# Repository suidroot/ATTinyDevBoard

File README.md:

# ATTinyDevBoardv1
An ATTiny85 Dev Board

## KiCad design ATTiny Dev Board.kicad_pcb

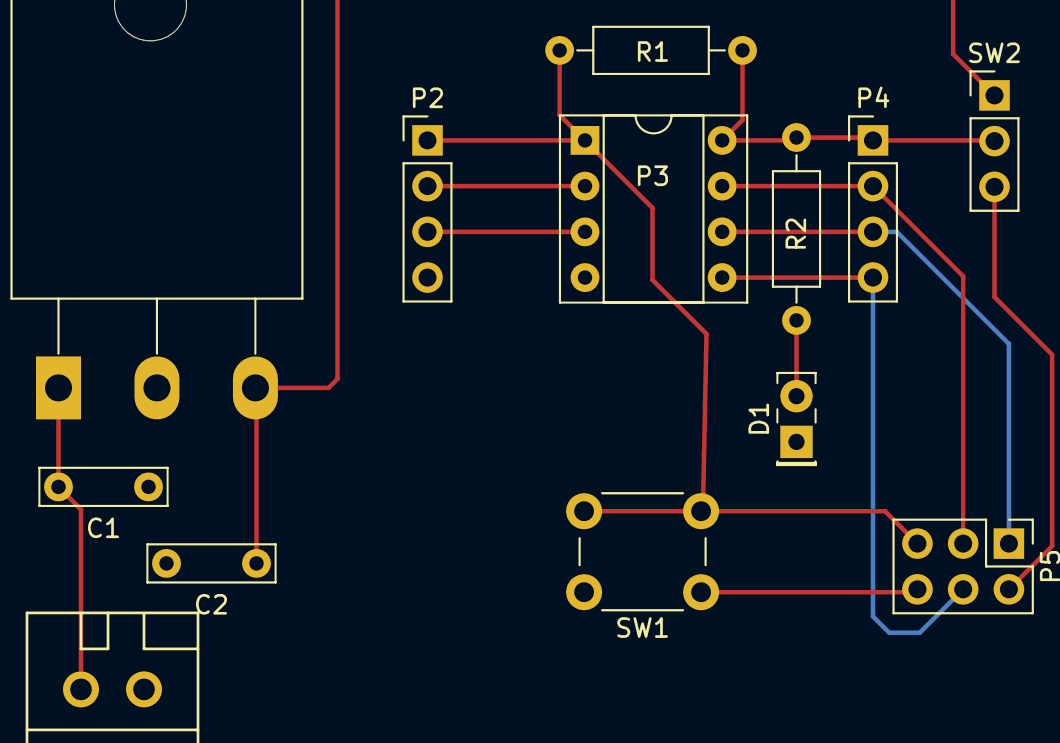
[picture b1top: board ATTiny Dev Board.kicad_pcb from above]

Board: 2 copper layers, 13 parts (0 on the bottom side), 12 nets.

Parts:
C1, C2: 100nF; C_Rect_L7.0mm_W2.0mm_P5.00mm
D1: LED; LED_Rectangular_W5.0mm_H2.0mm
P1: MOLEX_CONN_01X02; WAGO_734_2pin_Straight
P2, P4: CONN_01X04; Pin_Header_Straight_1x04_Pitch2.54mm
P3: DIL8; DIP-8_W7.62mm_Socket
P5: CONN_02X03; Pin_Header_Straight_2x03_Pitch2.54mm
R1: 10K; R_Axial_DIN0207_L6.3mm_D2.5mm_P10.16mm_Horizontal
R2: 220; R_Axial_DIN0207_L6.3mm_D2.5mm_P10.16mm_Horizontal
SW1: SW_Push_Dual; SW_PUSH_6mm
SW2: SW_SPDT; Socket_Strip_Straight_1x03_Pitch2.54mm
U1: LM7805CT; TO-218_SOT93_Horizontal

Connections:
GND: C1.1, C2.2, D1.1, P1.1, P2.4, P3.4, P5.6, SW1.1, U1.2
unnamed: C1.2, P1.2, U1.1
unnamed: D1.2, R2.1
unnamed: P2.2, P3.2
unnamed: P2.3, P3.3
unnamed: P3.5, P4.4, P5.4
unnamed: P3.6, P4.3, P5.1
unnamed: P3.7, P4.2, P5.3
unnamed: P5.2, SW2.3
PWR: P3.8, P4.1, R1.1, R2.2, SW2.2
RST: P2.1, P3.1, P5.5, R1.2, SW1.2
Vcc7805: C2.1, SW2.1, U1.3

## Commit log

2018-02-18 Update Git ignore
2018-02-18 Laid out Board file
